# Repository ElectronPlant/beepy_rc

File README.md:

# BeepyRC
Hobby project to make a RC rover platform using spare RC parts. The goal of this project is to develop a complete platform to support long term RC assisted missions.

Content summary

    * The platform is built on a custom PCB based on a STM32F4 microcontroller.
    * The firmware is implemented using FreeRTOS for simple and reliable multitasking and real-time operation.
    * The enclosure is fully 3d printable.
    * Support for off-the-shelf RC components with SBUS, 5V VTX power output, 3x standard servo outputs.

## Release 1 - [PoC] Nerf Blaster FPV Rover
Minimal-feature rover to support a simple, yet fun mission: exploring the house and firing a Nerf blaster in FPV (First-Person View).

The rover enables you to explore the house remotely using the RC interface and the FPV live feed provided by the video transmitter (VTX). The Nerf blaster and the VTX are mounted on a servo-operated arm, which controls their yaw and pitch angles. The arm provides two extra degrees of freedom to easily explore the room and aim the blaster. Once the target has been acquired, take the shot remotely using the aux channels of the RC remote.

### Complete Rover

### Custom PCB

### Rover

---

# Documentation
For more information about the project check the documentation in ```docs/``` or deplay with [mkdocs](https://www.mkdocs.org/)

## Installing MKDOCS
run:
```
pip install mkdocs
```
or:
```
python -m pip install mkdocs
```

### Install the Material theme:
```
pip install mkdocs-material
```
or:
```
python -m pip install mkdocs-material
```

### Install mkdoxy
```
pip install mkdoxy
```
or
```
python -m pip install mkdoxy
```

### Install Doxygen
The installation procedure depends on the operating system, see: [Doxygen docs](https://www.doxygen.nl/manual/install.html)

For ubuntu:
```
sudo apt-get install doxygen
```

### Deploy docs
```
mkdocs serve
```

then the documentation will be served at:
```
http://127.0.0.1:8000/
```

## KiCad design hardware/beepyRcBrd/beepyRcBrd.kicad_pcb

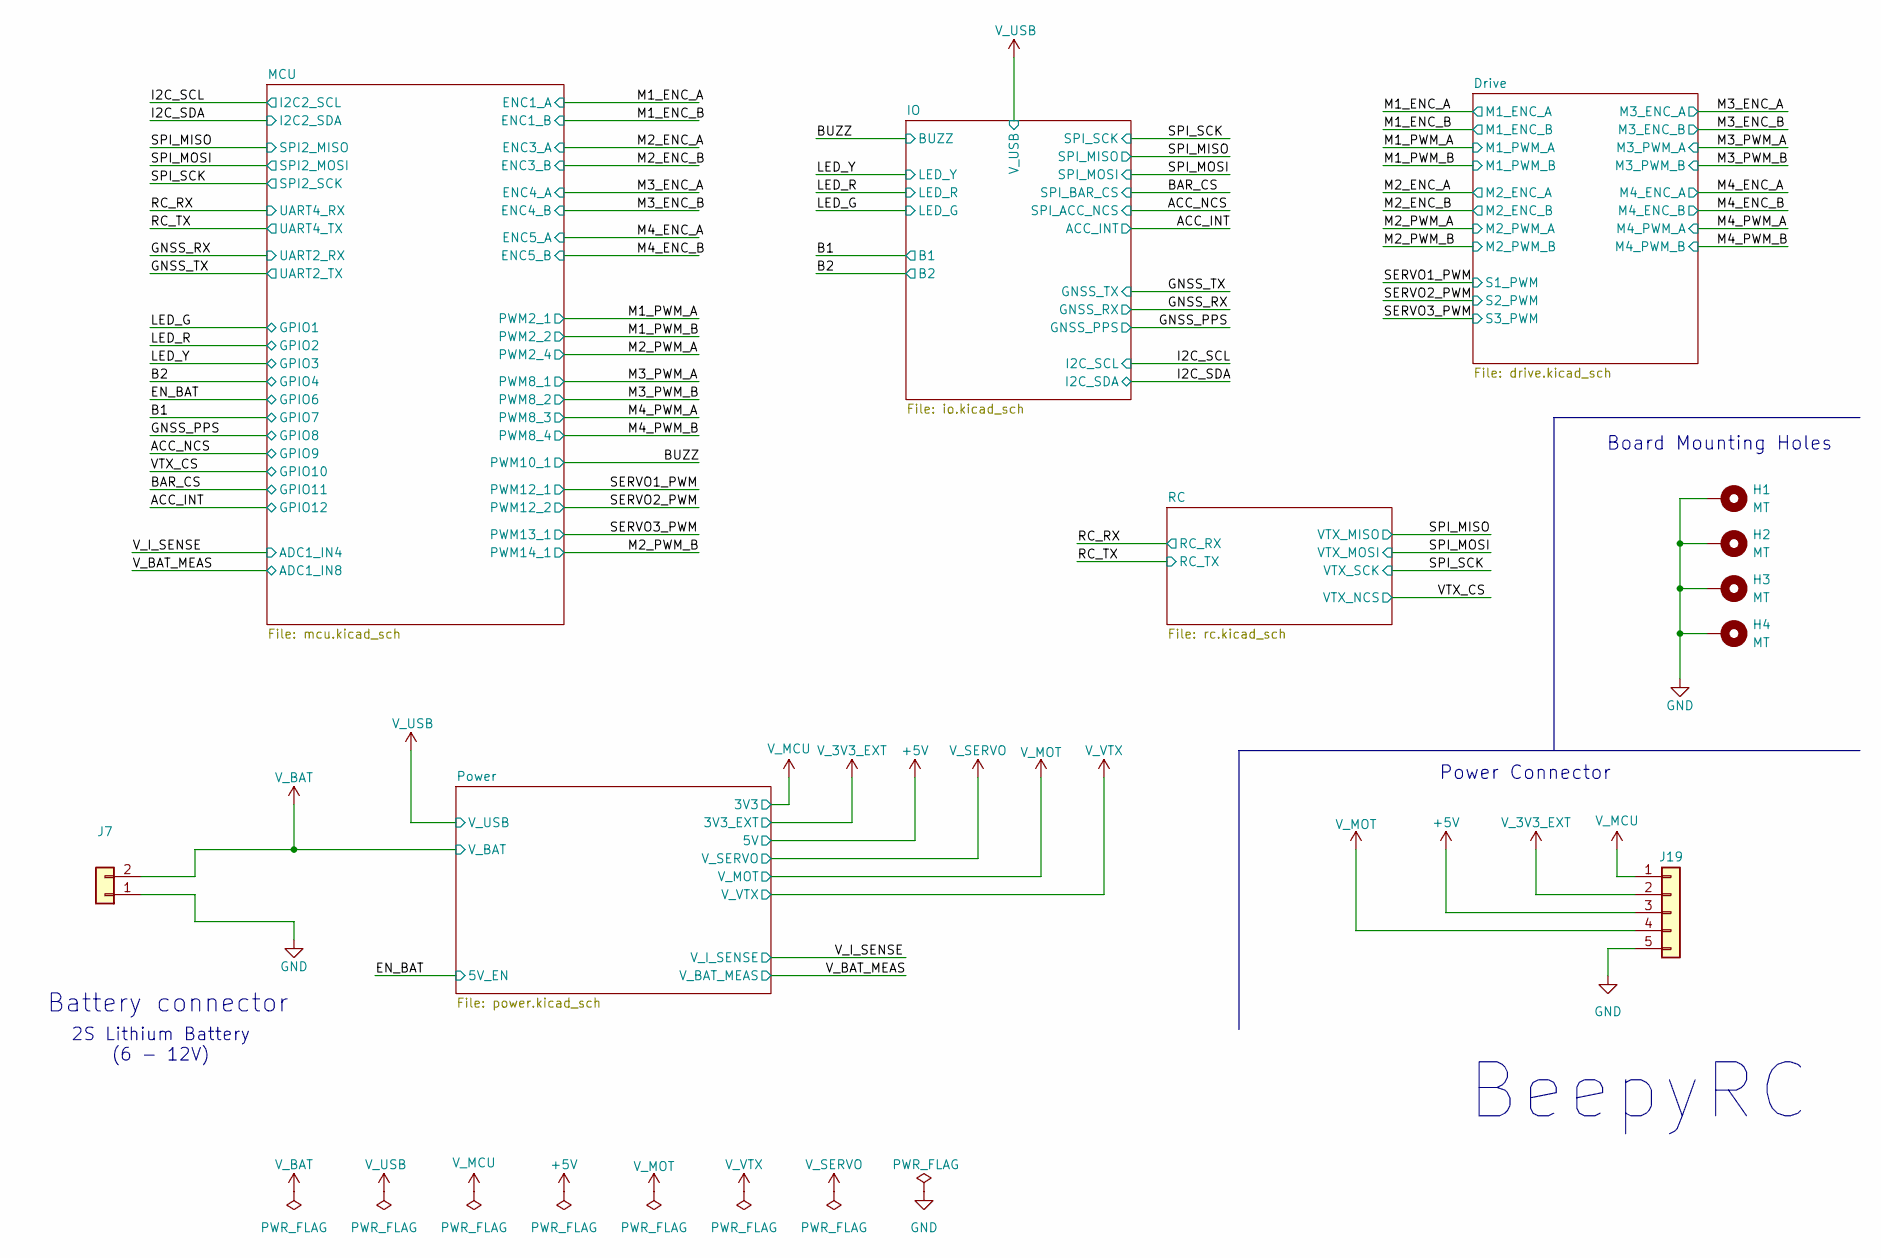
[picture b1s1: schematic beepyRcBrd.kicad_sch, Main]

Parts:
H1, H2, H3, H4: MT; MountingHole_4.3mm_M4_DIN965_Pad_TopBottom
J7: Conn_01x02; CONN-TH_P5.00_KF301-5.0-2P
J19: Conn_01x05; CONN-TH_5P-P3.50_DORABO_DB125-3.5-5P-GN-S

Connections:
+5V: J19.3; also elsewhere on the board
GND: H1.1, H2.1, H3.1, H4.1, J7.1, J19.5; also elsewhere on the board
V_3V3_EXT: J19.2; also elsewhere on the board
V_BAT: J7.2; also elsewhere on the board
V_MCU: J19.1; also elsewhere on the board
V_MOT: J19.4; also elsewhere on the board

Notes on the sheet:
Battery connector
2S Lithium Battery (6 - 12V)
Power Connector
BeepyRC
Board Mounting Holes

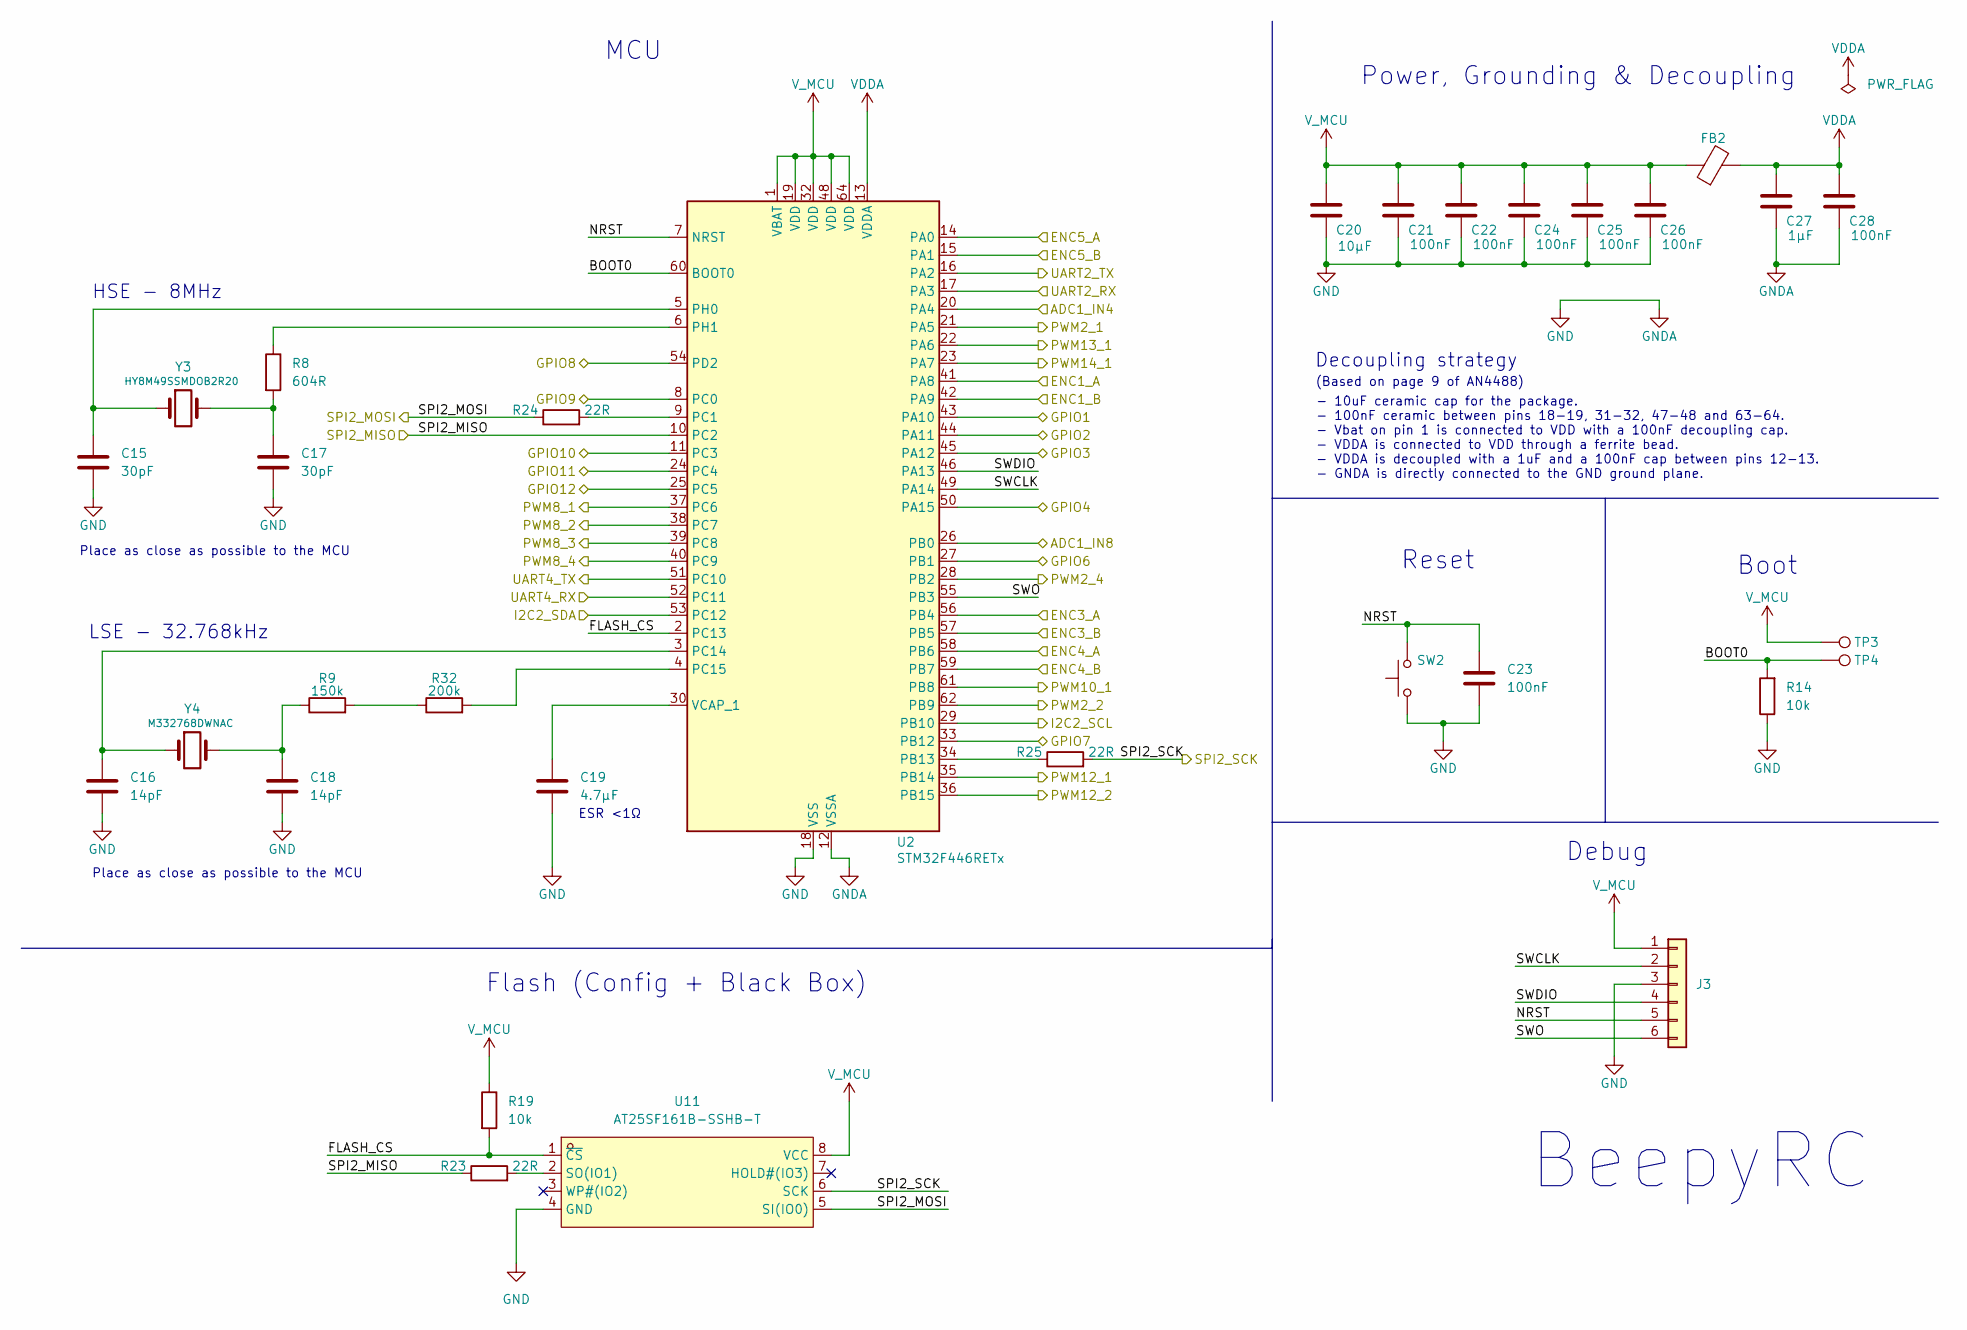
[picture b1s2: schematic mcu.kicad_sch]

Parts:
C15, C17: 30pF; C_0603_1608Metric_Pad1.08x0.95mm_HandSolder
C16, C18: 14pF; C_0603_1608Metric_Pad1.08x0.95mm_HandSolder
C19: 4.7μF; C_0603_1608Metric_Pad1.08x0.95mm_HandSolder
C20: 10μF; C_0603_1608Metric_Pad1.08x0.95mm_HandSolder
C21, C22, C23, C24, C25, C26, C28: 100nF; C_0603_1608Metric_Pad1.08x0.95mm_HandSolder
C27: 1μF; C_0603_1608Metric_Pad1.08x0.95mm_HandSolder
FB2: FerriteBead; R_0603_1608Metric_Pad0.98x0.95mm_HandSolder
J3: Conn_01x06; PinHeader_1x06_P2.54mm_Vertical
R8: 604R; R_0603_1608Metric_Pad0.98x0.95mm_HandSolder
R9: 150k; R_0603_1608Metric_Pad0.98x0.95mm_HandSolder
R14, R19: 10k; R_0603_1608Metric_Pad0.98x0.95mm_HandSolder
R23, R24, R25: 22R; R_0603_1608Metric_Pad0.98x0.95mm_HandSolder
R32: 200k; R_0603_1608Metric_Pad0.98x0.95mm_HandSolder
SW2: SW_Push; SW-SMD_L3.9-W3.0-P4.45
TP3, TP4: TestPoint; TestPoint_Pad_D1.0mm
U2: STM32F446RETx; LQFP-64_10x10mm_P0.5mm
U11: AT25SF161B-SSHB-T; SOP-8_L4.9-W3.9-P1.27-LS6.0-BL; LCSC Part C5555631
Y3: HY8M49SSMDOB2R20; CRYSTAL-SMD_L11.4-W4.7-LS12.7
Y4: M332768DWNAC; OSC-SMD_2P-L7.4-W3.1-LS8.0

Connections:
/ACC_INT: U2.25 (PC5); also elsewhere on the board
/ACC_NCS: U2.8 (PC0); also elsewhere on the board
/B1: U2.33 (PB12); also elsewhere on the board
/B2: U2.50 (PA15); also elsewhere on the board
/BAR_CS: U2.24 (PC4); also elsewhere on the board
/BUZZ: U2.61 (PB8); also elsewhere on the board
/EN_BAT: U2.27 (PB1); also elsewhere on the board
/GNSS_PPS: U2.54 (PD2); also elsewhere on the board
/GNSS_RX: U2.17 (PA3); also elsewhere on the board
/GNSS_TX: U2.16 (PA2); also elsewhere on the board
/I2C_SCL: U2.29 (PB10); also elsewhere on the board
/I2C_SDA: U2.53 (PC12); also elsewhere on the board
/LED_G: U2.43 (PA10); also elsewhere on the board
/LED_R: U2.44 (PA11); also elsewhere on the board
/LED_Y: U2.45 (PA12); also elsewhere on the board
/M1_ENC_A: U2.41 (PA8); also elsewhere on the board
/M1_ENC_B: U2.42 (PA9); also elsewhere on the board
/M1_PWM_A: U2.21 (PA5); also elsewhere on the board
/M1_PWM_B: U2.62 (PB9); also elsewhere on the board
/M2_ENC_A: U2.56 (PB4); also elsewhere on the board
/M2_ENC_B: U2.57 (PB5); also elsewhere on the board
/M2_PWM_A: U2.28 (PB2); also elsewhere on the board
/M2_PWM_B: U2.23 (PA7); also elsewhere on the board
/M3_ENC_A: U2.58 (PB6); also elsewhere on the board
/M3_ENC_B: U2.59 (PB7); also elsewhere on the board
/M3_PWM_A: U2.37 (PC6); also elsewhere on the board
/M3_PWM_B: U2.38 (PC7); also elsewhere on the board
/M4_ENC_A: U2.14 (PA0); also elsewhere on the board
/M4_ENC_B: U2.15 (PA1); also elsewhere on the board
/M4_PWM_A: U2.39 (PC8); also elsewhere on the board
/M4_PWM_B: U2.40 (PC9); also elsewhere on the board
/MCU/BOOT0: R14.2, TP4.1, U2.60 (BOOT0)
/MCU/FLASH_CS: R19.2, U2.2 (PC13), U11.1 (~CS)
/MCU/NRST: C23.1, J3.5, SW2.2, U2.7 (NRST)
/MCU/SWCLK: J3.2, U2.49 (PA14)
/MCU/SWDIO: J3.4, U2.46 (PA13)
/MCU/SWO: J3.6, U2.55 (PB3)
/RC_RX: U2.52 (PC11); also elsewhere on the board
/RC_TX: U2.51 (PC10); also elsewhere on the board
/SERVO1_PWM: U2.35 (PB14); also elsewhere on the board
/SERVO2_PWM: U2.36 (PB15); also elsewhere on the board
/SERVO3_PWM: U2.22 (PA6); also elsewhere on the board
/SPI_MISO: R23.1, U2.10 (PC2); also elsewhere on the board
/SPI_MOSI: R24.1, U11.5 (SI(IO0)); also elsewhere on the board
/SPI_SCK: R25.2, U11.6 (SCK); also elsewhere on the board
/VTX_CS: U2.11 (PC3); also elsewhere on the board
/V_BAT_MEAS: U2.26 (PB0); also elsewhere on the board
/V_I_SENSE: U2.20 (PA4); also elsewhere on the board
GND: C15.2, C16.2, C17.2, C18.2, C19.2, C20.2, C21.2, C22.2, C23.2, C24.2, C25.2, C26.2, C27.2, C28.2, J3.3, R14.1, SW2.1, U2.12 (VSSA), U2.18 (VSS), U2.31 (VSS), U2.47 (VSS), U2.63 (VSS), U11.4 (GND); also elsewhere on the board
unnamed: C17.1, R8.2, Y3.2
unnamed: C18.1, R9.1, Y4.2
unnamed: R9.2, R32.1
unnamed: R25.1, U2.34 (PB13)
unnamed: R24.2, U2.9 (PC1)
unnamed: C16.1, U2.3 (PC14), Y4.1
unnamed: R32.2, U2.4 (PC15)
unnamed: C15.1, U2.5 (PH0), Y3.1
unnamed: R8.1, U2.6 (PH1)
unnamed: C19.1, U2.30 (VCAP_1)
unnamed: R23.2, U11.2 (SO(IO1))
VDDA: C27.1, C28.1, FB2.2, U2.13 (VDDA)
V_MCU: C20.1, C21.1, C22.1, C24.1, C25.1, C26.1, FB2.1, J3.1, R19.1, TP3.1, U2.1 (VBAT), U2.19 (VDD), U2.32 (VDD), U2.48 (VDD), U2.64 (VDD), U11.8 (VCC); also elsewhere on the board

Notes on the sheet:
LSE - 32.768kHz
Decoupling strategy
Place as close as possible to the MCU
Reset
BeepyRC
ESR <1Ω
- 10uF ceramic cap for the package. - 100nF ceramic between pins 18-19, 31-32, 47-48 and 63-64. - Vbat on pin 1 is connected to VDD with a 100nF decoupling cap. - VDDA is connected to VDD through a ferrite bead. - VDDA is decoupled with a 1uF and a 100nF cap between pins 12-13. - GNDA is directly c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
MCU
Flash (Config + Black Box)
(Based on page 9 of AN4488)
Power, Grounding & Decoupling
Boot
HSE - 8MHz
Debug

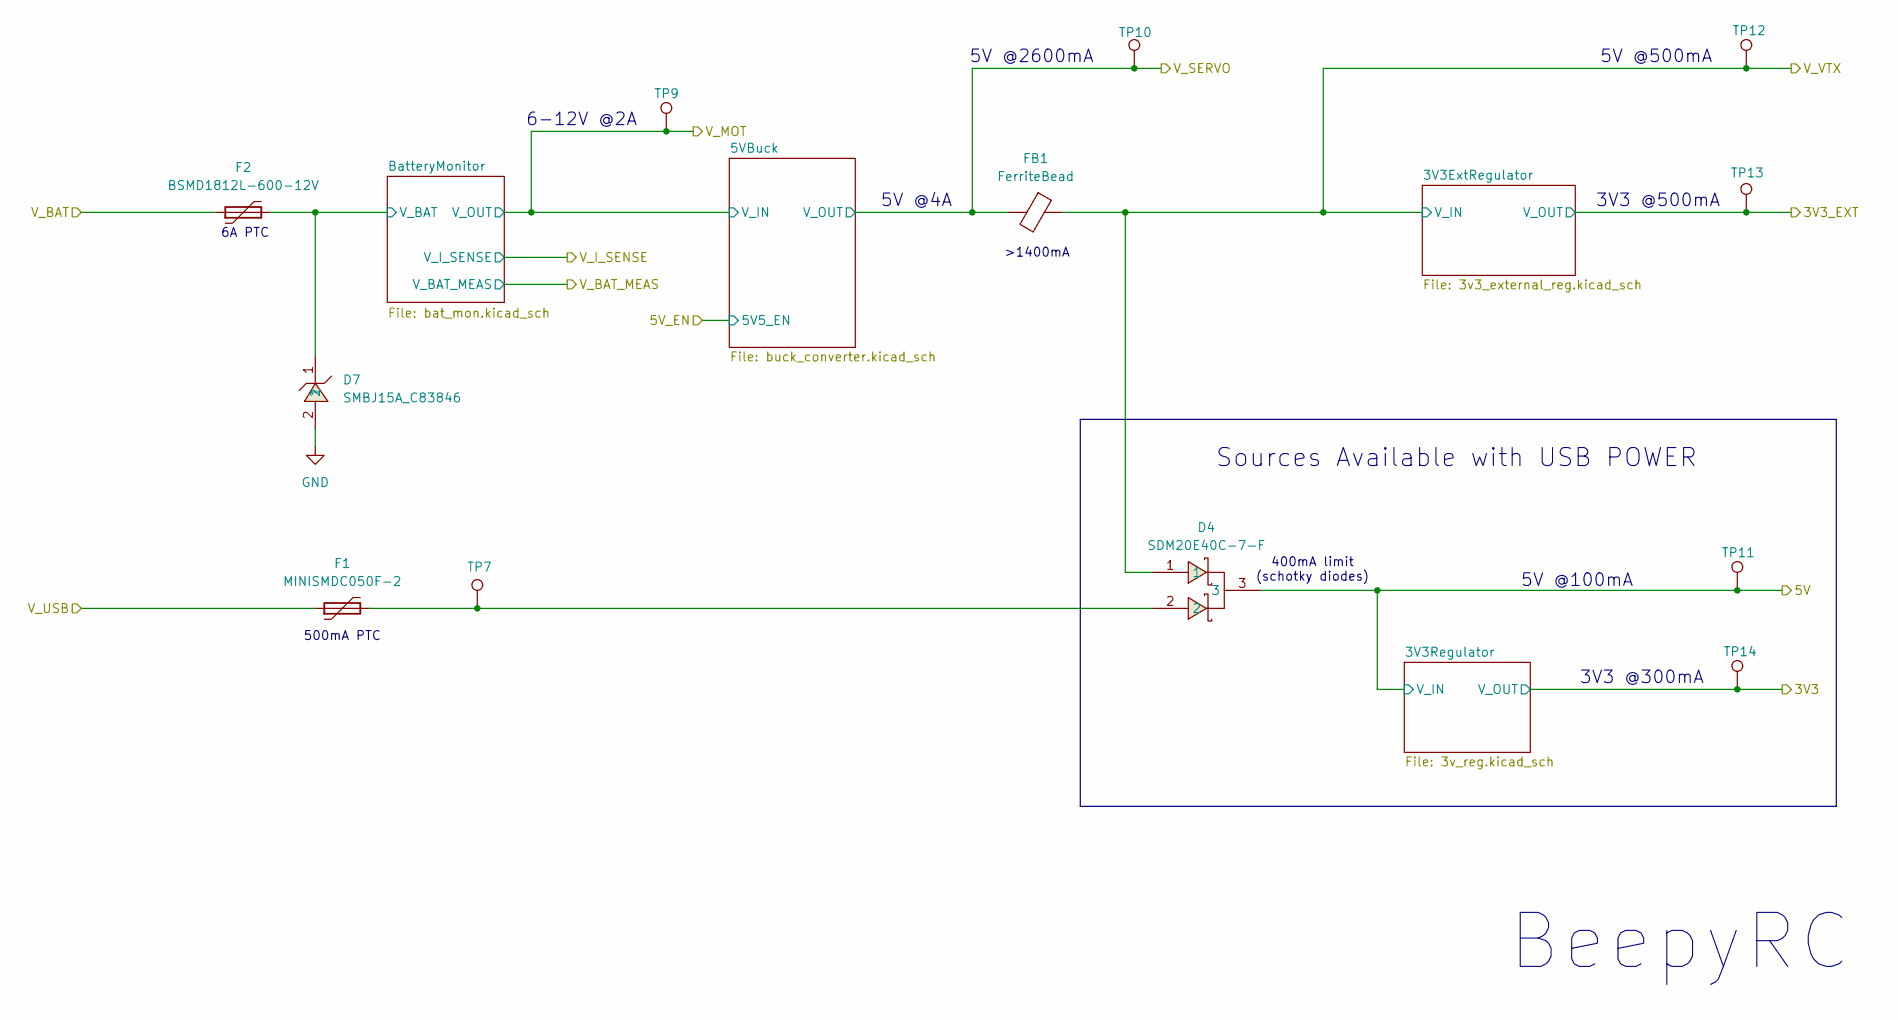
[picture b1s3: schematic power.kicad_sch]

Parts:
D4: SDM20E40C-7-F; SOT-23-3_L2.9-W1.6-P1.90-LS2.8-BR; LCSC Part C139437
D7: SMBJ15A_C83846; SMB_L4.6-W3.6-LS5.3-RD; LCSC Part C83846
F1: MINISMDC050F-2; Fuse_1812_4532Metric_Pad1.30x3.40mm_HandSolder
F2: BSMD1812L-600-12V; Fuse_1812_4532Metric_Pad1.30x3.40mm_HandSolder
FB1: FerriteBead; R_0603_1608Metric_Pad0.98x0.95mm_HandSolder
TP7, TP9, TP10, TP11, TP12, TP13, TP14: TestPoint; TestPoint_Pad_D1.0mm

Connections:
+5V: D4.3, TP11.1; also elsewhere on the board
/Power/BatteryMonitor/V_BAT: D7.1, F2.2; also elsewhere on the board
GND: D7.2; also elsewhere on the board
unnamed: D4.2, F1.2, TP7.1
V_3V3_EXT: TP13.1; also elsewhere on the board
V_BAT: F2.1; also elsewhere on the board
V_MCU: TP14.1; also elsewhere on the board
V_MOT: TP9.1; also elsewhere on the board
V_SERVO: FB1.2, TP10.1; also elsewhere on the board
V_USB: F1.1; also elsewhere on the board
V_VTX: D4.1, FB1.1, TP12.1; also elsewhere on the board

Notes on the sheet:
400mA limit (schotky diodes)
6A PTC
5V @2600mA
3V3 @500mA
Sources Available with USB POWER
5V @100mA
3V3 @300mA
500mA PTC
5V @4A
6-12V @2A
>1400mA
BeepyRC
5V @500mA

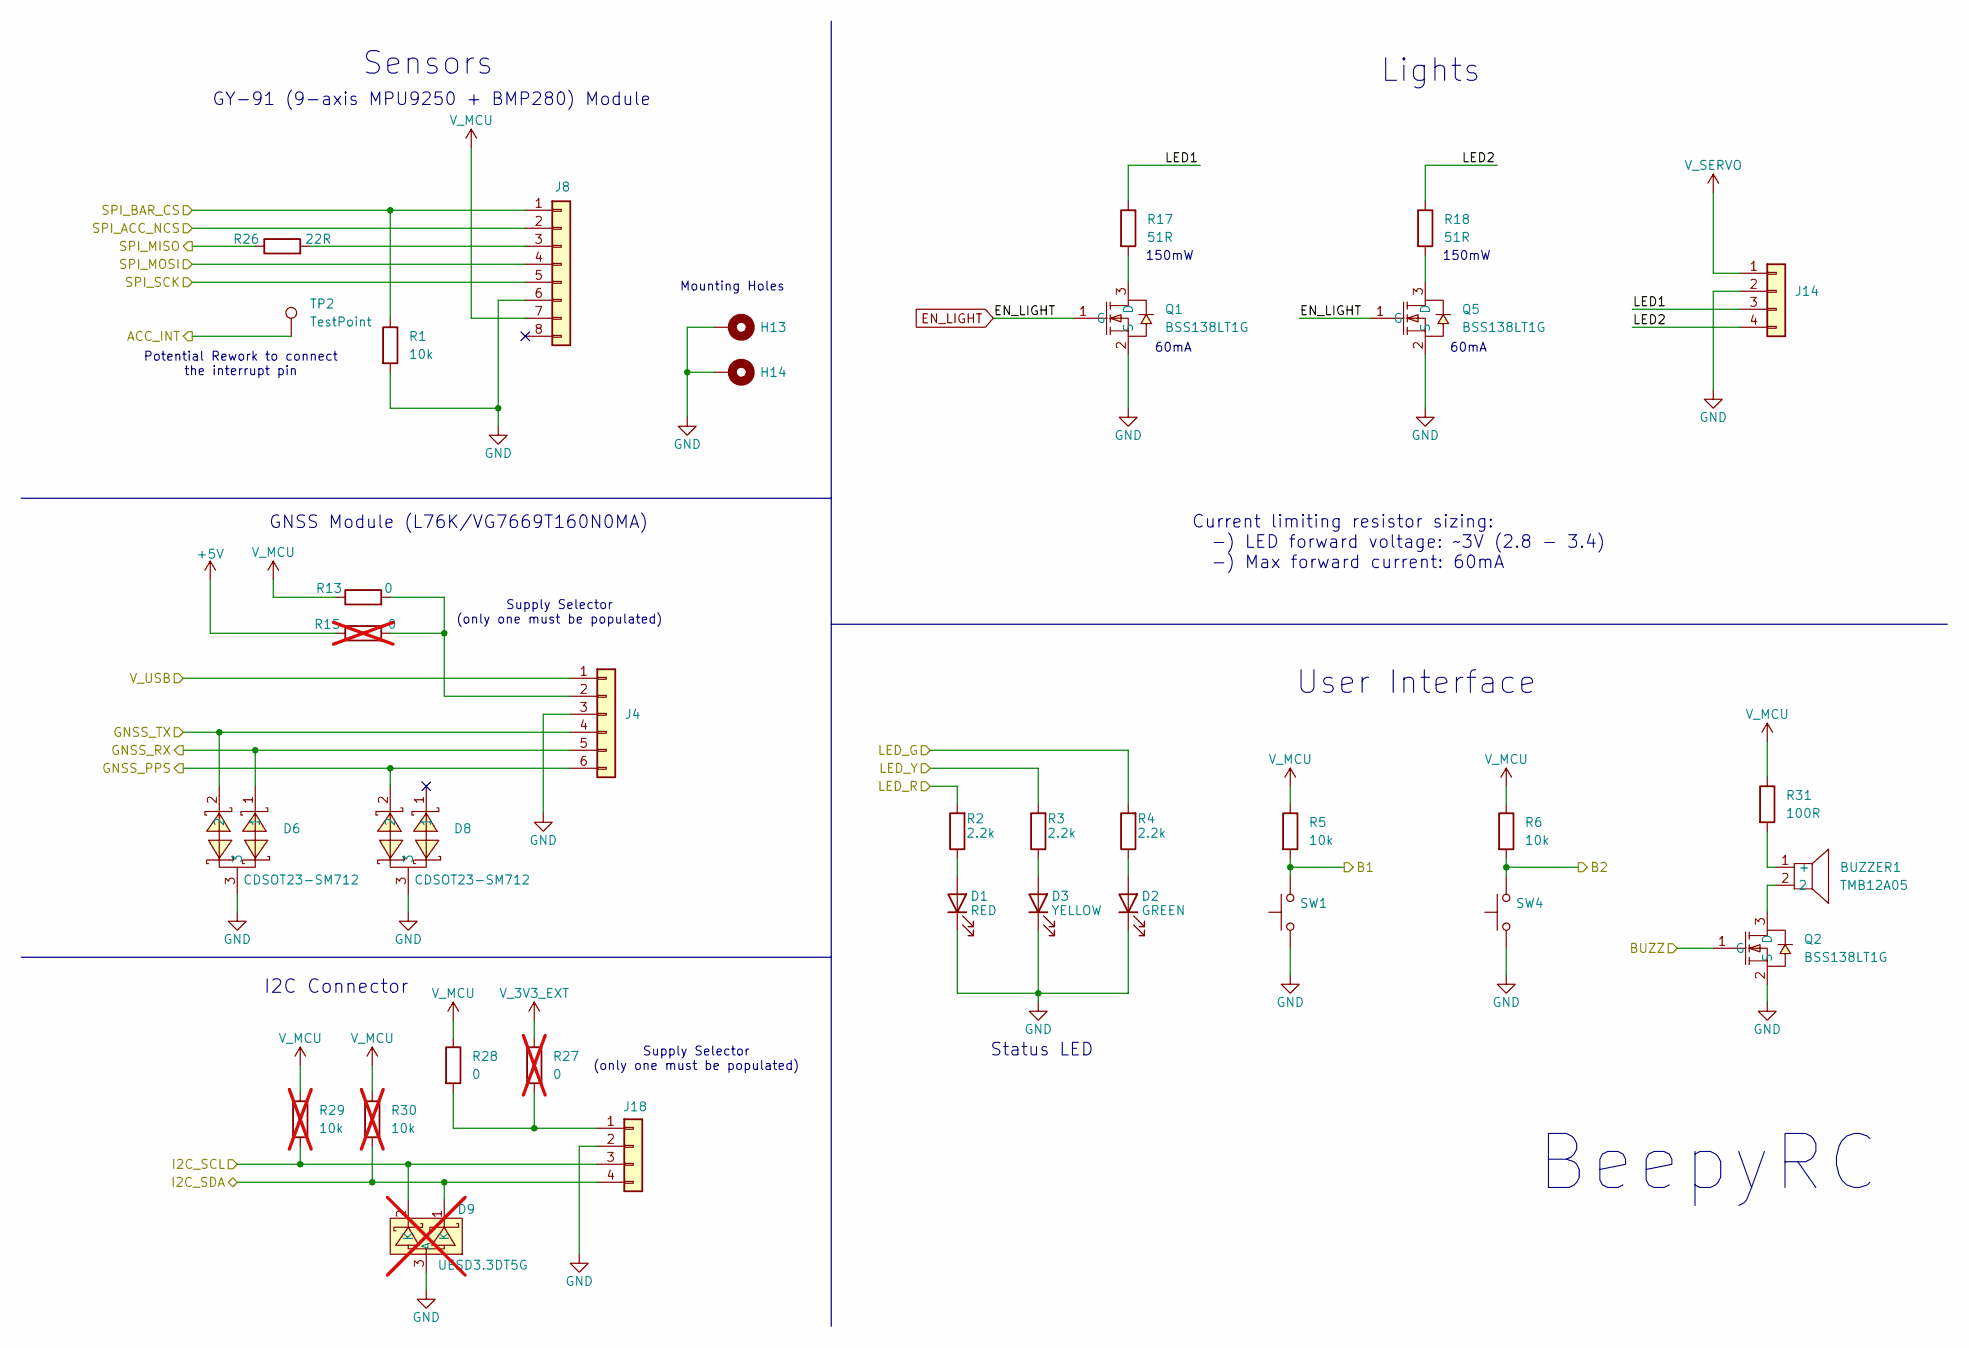
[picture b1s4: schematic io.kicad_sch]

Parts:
BUZZER1: TMB12A05; BUZ-TH_BD12.0-P7.60-D0.6-FD; LCSC Part C96093
D1: RED; LED_0603_1608Metric_Pad1.05x0.95mm_HandSolder
D2: GREEN; LED_0603_1608Metric_Pad1.05x0.95mm_HandSolder
D3: YELLOW; LED_0603_1608Metric_Pad1.05x0.95mm_HandSolder
D6, D8: CDSOT23-SM712; SOT-23_L2.9-W1.3-P1.90-LS2.4-BR; LCSC Part C404012
D9: UESD3.3DT5G; SOT-723_L1.2-W0.8-P0.40-LS1.2-BR; LCSC Part C233435; not fitted
H13, H14: MT; MountingHole_4.3mm_M4_DIN965_Pad_TopBottom
J4: Conn_01x06; PinHeader_1x06_P2.54mm_Vertical
J8: Conn_01x08; gy91
J14, J18: Conn_01x04; PinHeader_1x04_P2.54mm_Vertical
Q1, Q2, Q5: BSS138LT1G; SOT-23-3_L2.9-W1.6-P1.90-LS2.8-BR; LCSC Part C82045
R1, R5, R6: 10k; R_0603_1608Metric_Pad0.98x0.95mm_HandSolder
R2, R3, R4: 2.2k; R_0603_1608Metric_Pad0.98x0.95mm_HandSolder
R13, R28: 0; R_0603_1608Metric_Pad0.98x0.95mm_HandSolder
R15, R27: 0; R_0603_1608Metric_Pad0.98x0.95mm_HandSolder; not fitted
R17, R18: 51R; R_0603_1608Metric_Pad0.98x0.95mm_HandSolder
R26: 22R; R_0603_1608Metric_Pad0.98x0.95mm_HandSolder
R29, R30: 10k; R_0603_1608Metric_Pad0.98x0.95mm_HandSolder; not fitted
R31: 100R; R_0603_1608Metric_Pad0.98x0.95mm_HandSolder
SW1, SW4: SW_Push; SW-SMD_L3.9-W3.0-P4.45
TP2: TestPoint; TestPoint_Pad_D2.5mm

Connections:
+5V: R15.1; also elsewhere on the board
/ACC_INT: TP2.1; also elsewhere on the board
/ACC_NCS: J8.2; also elsewhere on the board
/B1: R5.2, SW1.2; also elsewhere on the board
/B2: R6.2, SW4.2; also elsewhere on the board
/BAR_CS: J8.1, R1.1; also elsewhere on the board
/BUZZ: Q2.1 (G); also elsewhere on the board
/GNSS_PPS: D8.2, J4.6; also elsewhere on the board
/GNSS_RX: D6.1, J4.5; also elsewhere on the board
/GNSS_TX: D6.2, J4.4; also elsewhere on the board
/I2C_SCL: D9.2 (K), J18.3, R29.2; also elsewhere on the board
/I2C_SDA: D9.1 (K), J18.4, R30.2; also elsewhere on the board
/IO/LED1: J14.3, R17.1
/IO/LED2: J14.4, R18.1
/LED_G: R4.2; also elsewhere on the board
/LED_R: R2.2; also elsewhere on the board
/LED_Y: R3.2; also elsewhere on the board
/SPI_MISO: R26.1; also elsewhere on the board
/SPI_MOSI: J8.4; also elsewhere on the board
/SPI_SCK: J8.5; also elsewhere on the board
EN_LIGHT: Q1.1 (G), Q5.1 (G)
GND: D1.1 (K), D2.1 (K), D3.1 (K), D6.3, D8.3, D9.3 (A), H13.1, H14.1, J4.3, J8.6, J14.2, J18.2, Q1.2 (S), Q2.2 (S), Q5.2 (S), R1.2, SW1.1, SW4.1; also elsewhere on the board
unnamed: BUZZER1.1 (+), R31.2
unnamed: D1.2 (A), R2.1
unnamed: D2.2 (A), R4.1
unnamed: D3.2 (A), R3.1
unnamed: J4.2, R13.2, R15.2
unnamed: J8.3, R26.2
unnamed: J18.1, R27.2, R28.2
unnamed: Q1.3 (D), R17.2
unnamed: BUZZER1.2, Q2.3 (D)
unnamed: Q5.3 (D), R18.2
V_3V3_EXT: R27.1; also elsewhere on the board
V_MCU: J8.7, R5.1, R6.1, R13.1, R28.1, R29.1, R30.1, R31.1; also elsewhere on the board
V_SERVO: J14.1; also elsewhere on the board
V_USB: J4.1; also elsewhere on the board

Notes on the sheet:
150mW
60mA
BeepyRC
Lights
GNSS Module (L76K/VG7669T160N0MA)
User Interface
Supply Selector (only one must be populated)
Potential Rework to connect the interrupt pin
Status LED
GY-91 (9-axis MPU9250 + BMP280) Module
I2C Connector
Current limiting resistor sizing: -) LED forward voltage: ~3V (2.8 - 3.4) -) Max forward current: 60mA
Sensors
Mounting Holes

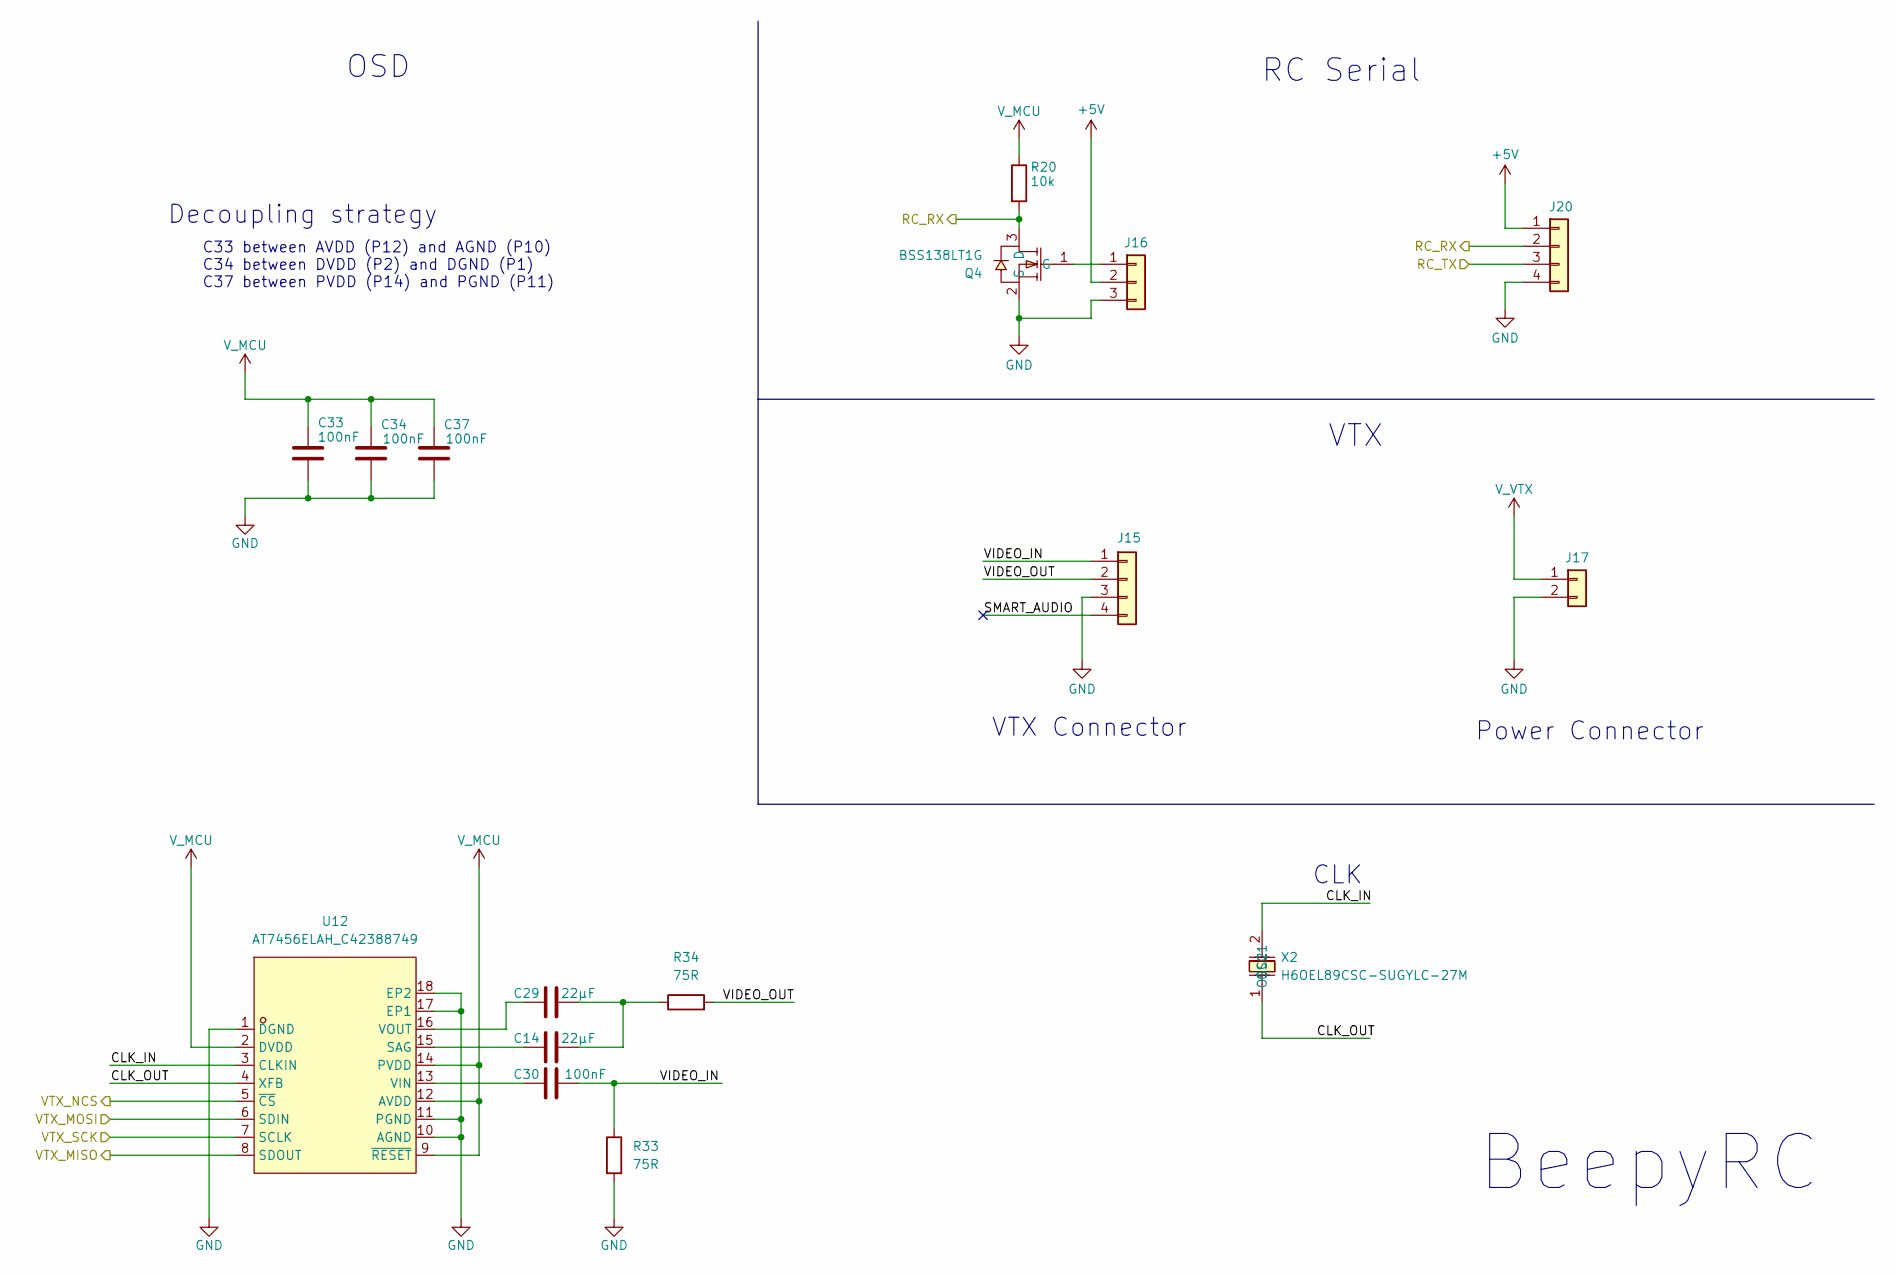
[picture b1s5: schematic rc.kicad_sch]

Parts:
C14, C29: 22μF; C_0603_1608Metric_Pad1.08x0.95mm_HandSolder
C30, C33, C34, C37: 100nF; C_0603_1608Metric_Pad1.08x0.95mm_HandSolder
J15, J20: Conn_01x04; PinHeader_1x04_P2.54mm_Vertical
J16: Conn_01x03; rc
J17: Conn_01x02; PinHeader_1x02_P2.54mm_Vertical
Q4: BSS138LT1G; SOT-23-3_L2.9-W1.6-P1.90-LS2.8-BR; LCSC Part C82045
R20: 10k; R_0603_1608Metric_Pad0.98x0.95mm_HandSolder
R33, R34: 75R; R_0603_1608Metric_Pad0.98x0.95mm_HandSolder
U12: AT7456ELAH_C42388749; LGA-16_L6.8-W4.0-P0.65-TL-2EP; LCSC Part C42388749
X2: H6OEL89CSC-SUGYLC-27M; HC-49S_L11.4-W4.8-LS12.7; LCSC Part C19078186

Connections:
+5V: J16.2, J20.1; also elsewhere on the board
/RC/CLK_IN: U12.3 (CLKIN), X2.2 (OSC2)
/RC/CLK_OUT: U12.4 (XFB), X2.1 (OSC1)
/RC/SMART_AUDIO: J15.4
/RC/VIDEO_IN: C30.2, J15.1, R33.1
/RC/VIDEO_OUT: J15.2, R34.2
/RC_RX: J20.2, Q4.3 (D), R20.2; also elsewhere on the board
/RC_TX: J20.3; also elsewhere on the board
/SPI_MISO: U12.8 (SDOUT); also elsewhere on the board
/SPI_MOSI: U12.6 (SDIN); also elsewhere on the board
/SPI_SCK: U12.7 (SCLK); also elsewhere on the board
/VTX_CS: U12.5 (~CS); also elsewhere on the board
GND: C33.2, C34.2, C37.2, J15.3, J16.3, J17.2, J20.4, Q4.2 (S), R33.2, U12.1 (DGND), U12.10 (AGND), U12.11 (PGND), U12.17 (EP1), U12.18 (EP2); also elsewhere on the board
unnamed: C14.2, C29.2, R34.1
unnamed: J16.1, Q4.1 (G)
unnamed: C14.1, U12.15 (SAG)
unnamed: C30.1, U12.13 (VIN)
unnamed: C29.1, U12.16 (VOUT)
V_MCU: C33.1, C34.1, C37.1, R20.1, U12.2 (DVDD), U12.9 (~RESET), U12.12 (AVDD), U12.14 (PVDD); also elsewhere on the board
V_VTX: J17.1; also elsewhere on the board

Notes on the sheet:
BeepyRC
OSD
VTX
VTX Connector
C33 between AVDD (P12) and AGND (P10) C34 between DVDD (P2) and DGND (P1) C37 between PVDD (P14) and PGND (P11)
CLK
Decoupling strategy
Power Connector
RC Serial

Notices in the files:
hardware/beepyRcBrd/3v3_external_reg.kicad_sch:
© David Arnaiz 2026
Licensed under CERN-OHL-S v2
